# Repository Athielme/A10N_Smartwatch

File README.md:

# A10N_Smartwatch
Created for the Purdue MILESTONES Smartwatch course, Summer 2020

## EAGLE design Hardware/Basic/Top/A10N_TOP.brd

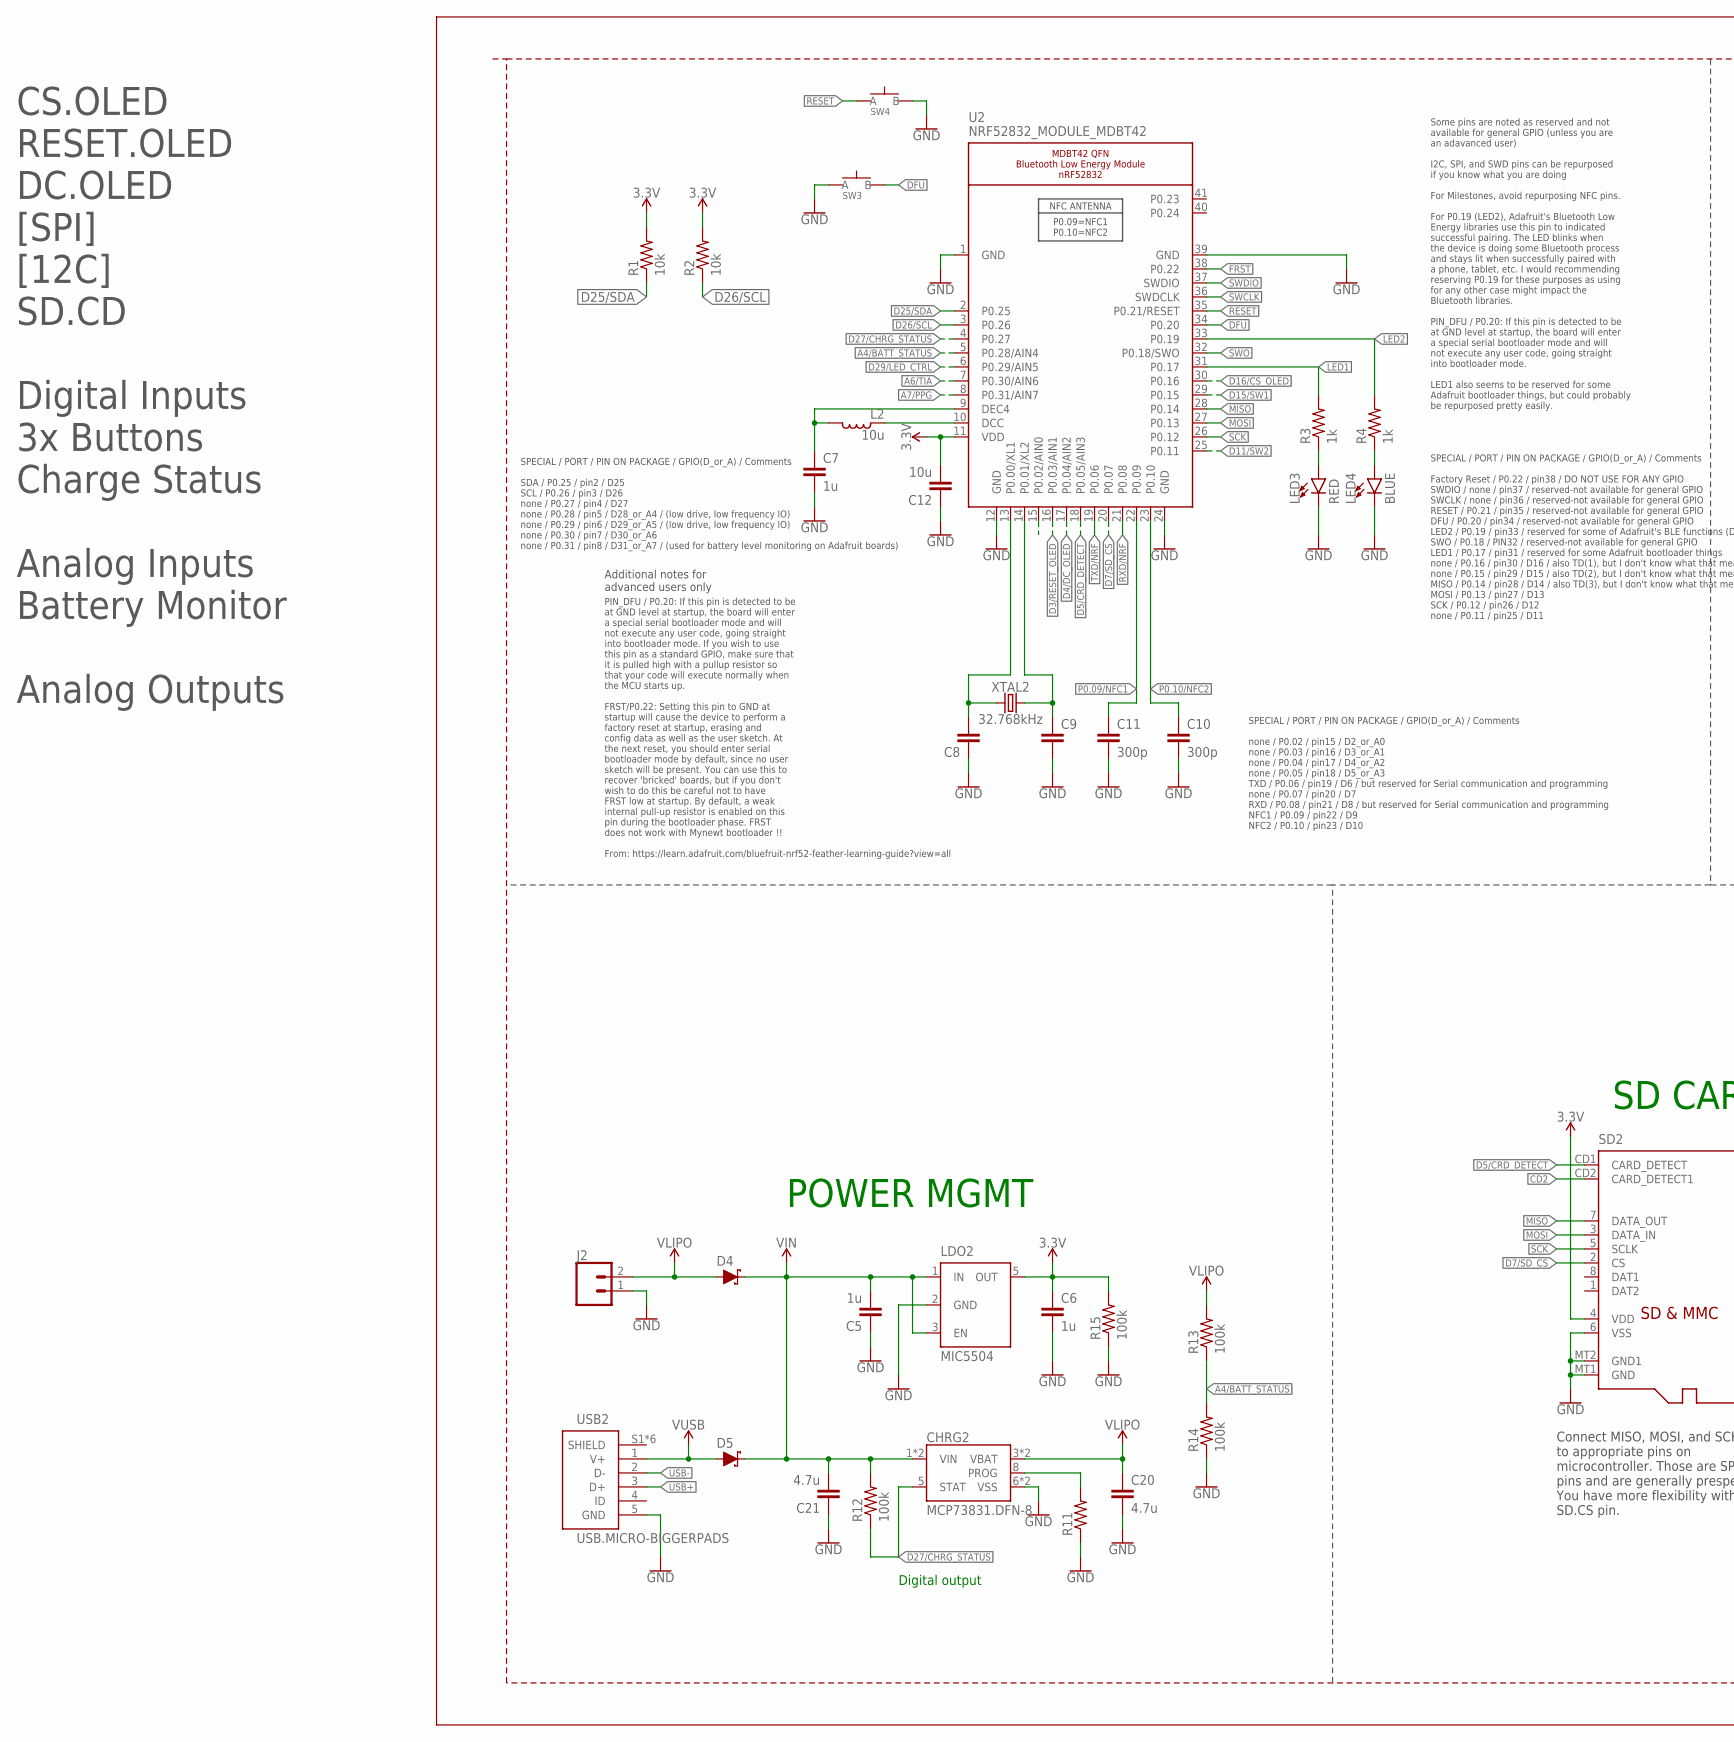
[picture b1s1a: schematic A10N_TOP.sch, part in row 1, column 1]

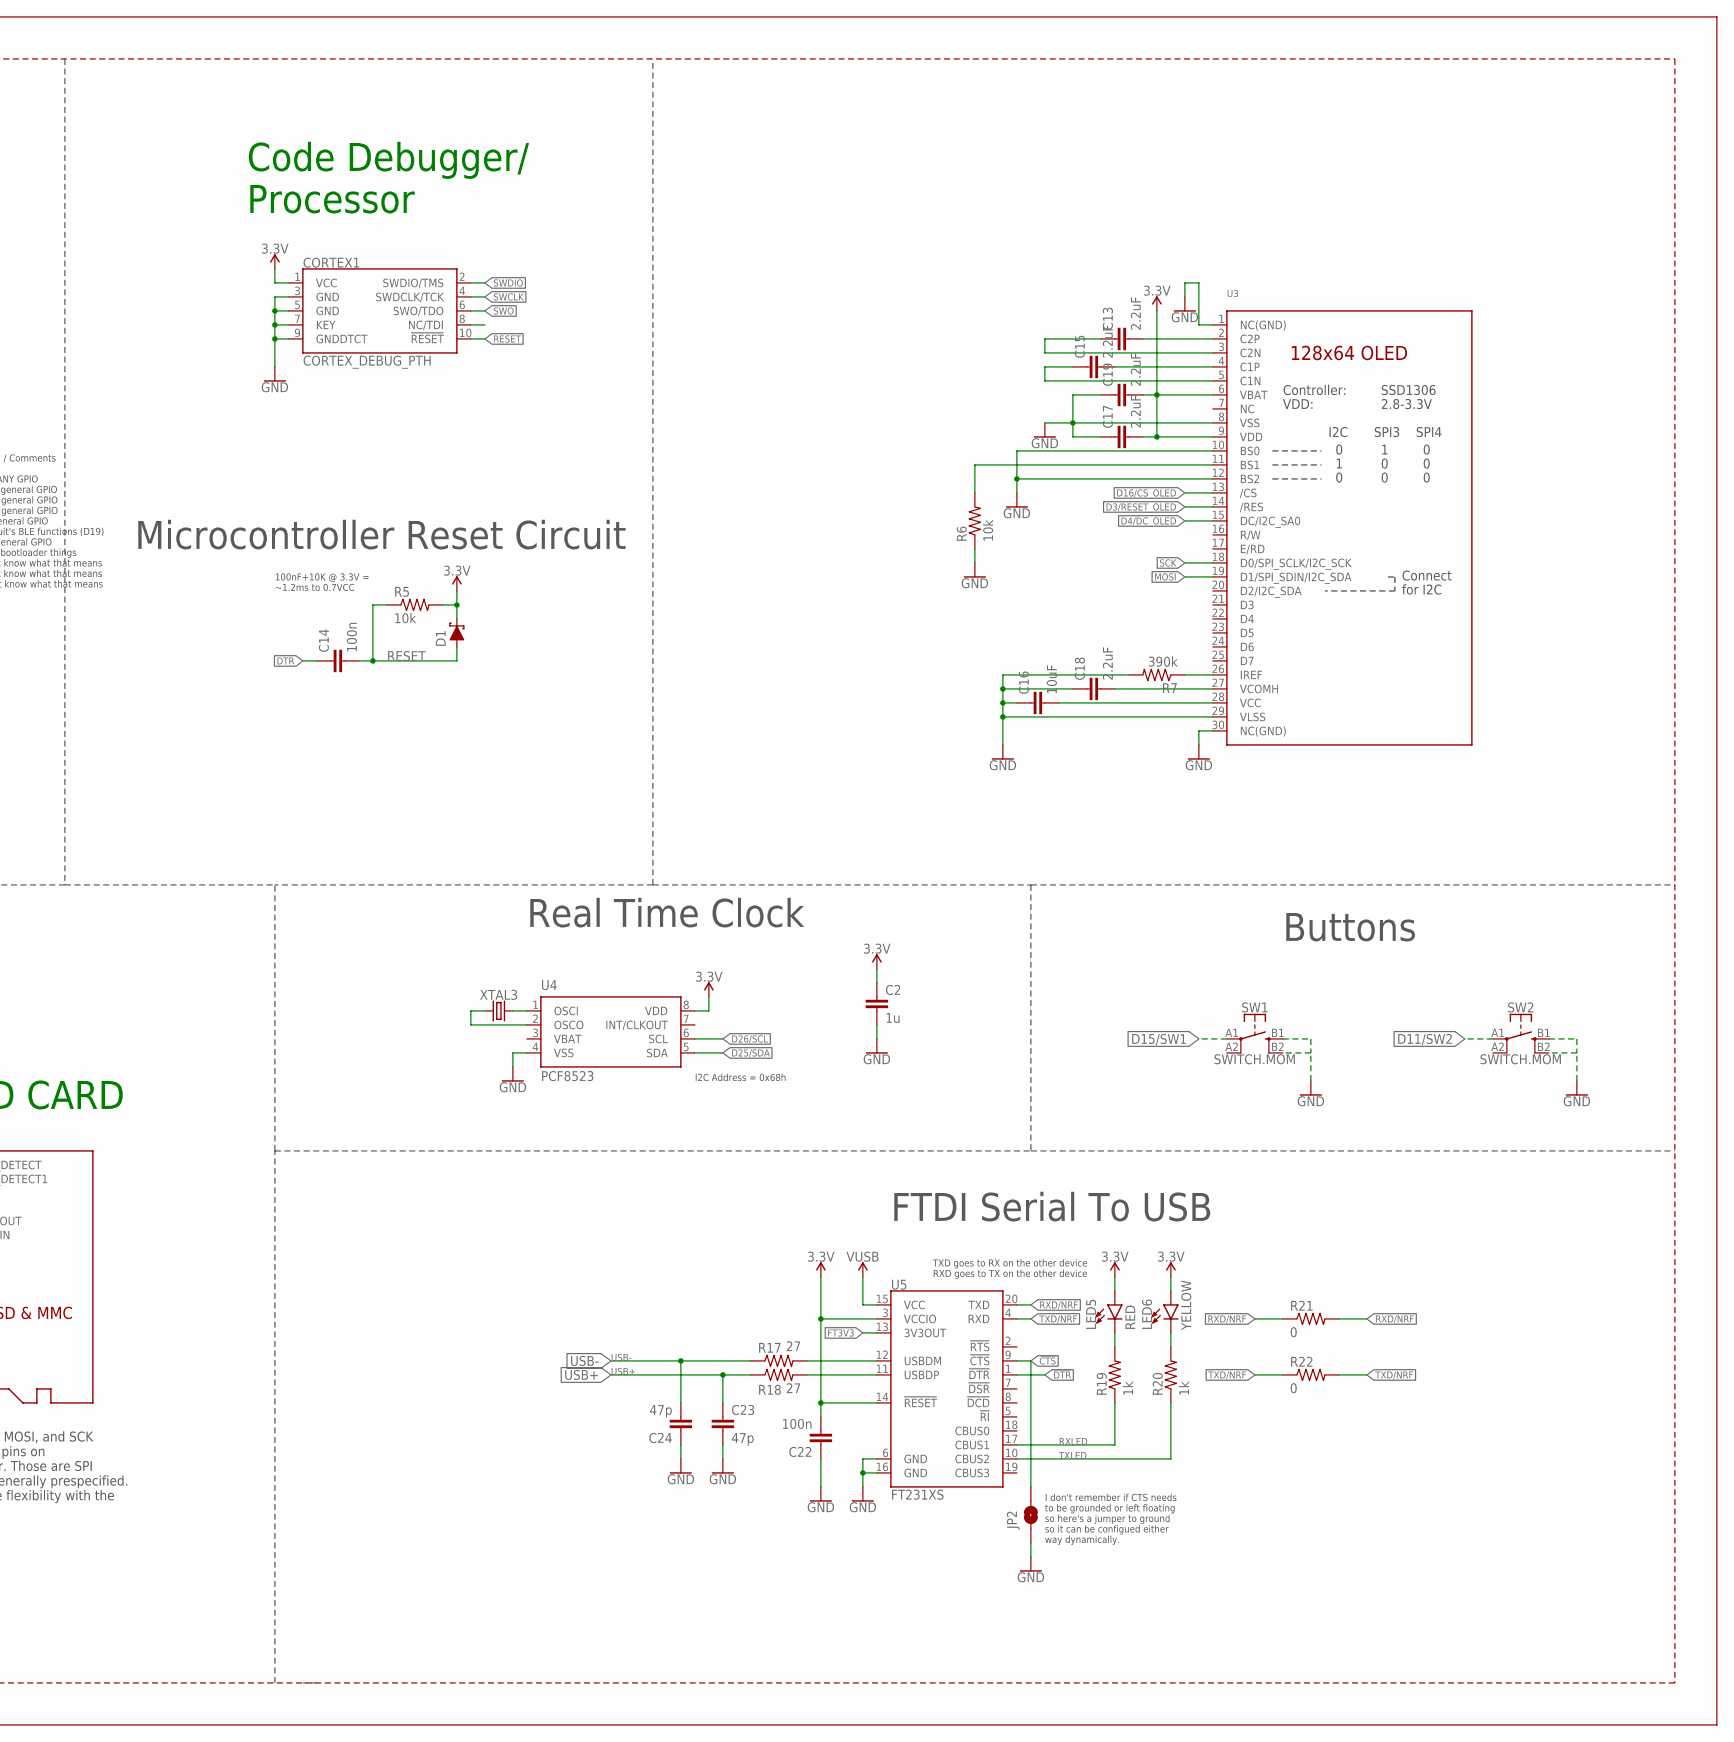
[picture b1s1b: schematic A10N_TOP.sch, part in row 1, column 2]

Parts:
C2, C5, C6, C7: 1u; C0603
C8, C9: CAPACITOR0603; C0603
C10, C11: 300p; C0603
C12: 10u; C0805
C13, C15, C17, C18, C19: 2.2uF; C0402
C14, C22: 100n; C0603
C16: 10uF; C0603
C20, C21: 4.7u; C0603
C23, C24: 47p; C0603
CHRG2: MCP73831.DFN-8; DFN-8-2X3MM
CORTEX1: CORTEX_DEBUG_PTH; 2X5-PTH-1.27MM
D1, D4, D5: SCHOTTKY-USC; USC
J2: CONN_02; 1X02
JP2: JUMPER-SMT_2_NO_SILK; SMT-JUMPER_2_NO_SILK
L2: 10u; L0603
LDO2: MIC5504; SOT23-5@1
LED3, LED5: RED; LED-0603
LED4: BLUE; LED-0603
LED6: YELLOW; LED-0603
R1, R2, R5, R6: 10k; R0603
R3, R4, R19, R20: 1k; R0603
R7: 390k; R0603
R11: RESISTOR0603; R0603
R12, R13, R14, R15: 100k; R0603
R17, R18: 27; R0603
R21, R22: 0; R0603
SD2: MICROSD
SW1, SW2: SWITCH.MOM; TACTILE_SWITCH_SMD_6.2MM_TALL
SW3, SW4: SPST-PTS830GG140-COPY.1-3; BUTTON-GULLWING
U2: NRF52832_MODULE_MDBT42; BLE_MODULE_RAYTAC_MDBT42
U3: DISP_OLED_UG-2864HSWEG01-NO-WRAPAROUND; UG-2864HSWEG01_0.96IN_NO-WRAPAROUND
U4: PCF8523; SO8; DIGIKEY 568-5306-1-ND
U5: FT231XS; SSOP20_L
USB2: USB.MICRO-BIGGERPADS; USB-MICRO-01.BIGGERPADS
XTAL2: 32.768kHz; 2-SMD.NOLEAD.2.0MMTO1.2MM
XTAL3: 32.7680kHz; 2-SMD.NOLEAD.2.0MMTO1.2MM

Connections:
3.3V: C2.1, C6.1, C12.2, C17.2, C19.2, C22.2, CORTEX1.1 (VCC), D1.- (C), LDO2.5 (OUT), LED5.A, LED6.A, R1.2, R2.2, R5.2, R15.2, SD2.4 (VDD), U2.11 (VDD), U3.6 (VBAT), U3.9 (VDD), U4.8 (VDD), U5.3 (VCCIO), U5.14 (!RESET)
!CTS: JP2.2, U5.9 (!CTS)
!DTR: U5.1 (!DTR)
A4/BATT_STATUS: R13.1, R14.2, U2.5 (P0.28/AIN4)
A6/TIA: U2.7 (P0.30/AIN6)
A7/PPG: U2.8 (P0.31/AIN7)
CD2: SD2.CD2 (CARD_DETECT1)
D3/RESET_OLED: U2.16 (P0.03/AIN1), U3.14 (/RES)
D4/DC_OLED: U2.17 (P0.04/AIN2), U3.15 (DC/I2C_SA0)
D5/CRD_DETECT: SD2.CD1 (CARD_DETECT), U2.18 (P0.05/AIN3)
D7/SD_CS: SD2.2 (CS), U2.20 (P0.07)
D11/SW2: SW2.A1 (1), U2.25 (P0.11)
D15/SW1: SW1.A1 (1), U2.29 (P0.15)
D16/CS_OLED: U2.30 (P0.16), U3.13 (/CS)
D25/SDA: R1.1, U2.2 (P0.25), U4.5 (SDA)
D26/SCL: R2.1, U2.3 (P0.26), U4.6 (SCL)
D27/CHRG_STATUS: CHRG2.5 (STAT), R12.1, U2.4 (P0.27)
D29/LED_CTRL: U2.6 (P0.29/AIN5)
DFU: SW3.3 (B), U2.34 (P0.20)
DTR: C14.1
FRST: U2.38 (P0.22)
FT3V3: U5.13 (3V3OUT)
GND: C2.2, C5.1, C6.2, C7.2, C8.1, C9.2, C10.2, C11.2, C12.1, C16.1, C17.1, C18.1, C19.1, C20.2, C21.1, C22.1, C23.2, C24.1, CHRG2.6 (VSS), CHRG2.EP (VSS), CORTEX1.3 (GND), CORTEX1.5 (GND), CORTEX1.7 (KEY), CORTEX1.9 (GNDDTCT), J2.1, JP2.1, LDO2.2 (GND), LED3.C, LED4.C, R6.1, R7.2, R11.1, R14.1, R15.1, SD2.6 (VSS), SD2.MT1 (GND), SD2.MT2 (GND1), SW1.B1 (3), SW1.B2 (4), SW2.B1 (3), SW2.B2 (4), SW3.1 (A), SW4.3 (B), U2.1 (GND), U2.12 (GND), U2.24 (GND), U2.39 (GND), U3.1 (NC(GND)), U3.8 (VSS), U3.10 (BS0), U3.12 (BS2), U3.29 (VLSS), U3.30 (NC(GND)), U4.4 (VSS), U5.6 (GND), U5.16 (GND), USB2.5 (GND)
LED1: R3.2, U2.31 (P0.17)
LED2: R4.2, U2.33 (P0.19)
MISO: SD2.7 (DATA_OUT), U2.28 (P0.14)
MOSI: SD2.3 (DATA_IN), U2.27 (P0.13), U3.19 (D1/SPI_SDIN/I2C_SDA)
unnamed: R6.2, U3.11 (BS1)
unnamed: R7.1, U3.26 (IREF)
unnamed: C13.2, U3.2 (C2P)
unnamed: C8.2, U2.13 (P0.00/XL1), XTAL2.P$1 (1)
unnamed: C13.1, U3.3 (C2N)
unnamed: C9.1, U2.14 (P0.01/XL2), XTAL2.P$2 (2)
unnamed: C15.2, U3.4 (C1P)
unnamed: C15.1, U3.5 (C1N)
unnamed: LED3.A, R3.1
unnamed: LED4.A, R4.1
unnamed: L2.1, U2.10 (DCC)
unnamed: C7.1, L2.2, U2.9 (DEC4)
unnamed: C16.2, U3.28 (VCC)
unnamed: C18.2, U3.27 (VCOMH)
unnamed: CHRG2.8 (PROG), R11.2
unnamed: R17.2, U5.12 (USBDM)
unnamed: R18.2, U5.11 (USBDP)
unnamed: LED5.C, R19.2
unnamed: LED6.C, R20.2
unnamed: U4.2 (OSCO), XTAL3.P$1 (1)
unnamed: U4.1 (OSCI), XTAL3.P$2 (2)
P0.09/NFC1: C11.1, U2.22 (P0.09)
P0.10/NFC2: C10.1, U2.23 (P0.10)
RESET: C14.2, CORTEX1.10 (!RESET), D1.+ (A), R5.1, SW4.1 (A), U2.35 (P0.21/RESET)
RXD/NRF: U2.21 (P0.08), U5.20 (TXD)
RXLED: R19.1, U5.17 (CBUS1)
SCK: SD2.5 (SCLK), U2.26 (P0.12), U3.18 (D0/SPI_SCLK/I2C_SCK)
SWCLK: CORTEX1.4 (SWDCLK/TCK), U2.36 (SWDCLK)
SWDIO: CORTEX1.2 (SWDIO/TMS), U2.37 (SWDIO)
SWO: CORTEX1.6 (SWO/TDO), U2.32 (P0.18/SWO)
TXD/NRF: U2.19 (P0.06), U5.4 (RXD)
TXLED: R20.1, U5.10 (CBUS2)
USB+: C23.1, R18.1, USB2.3 (D+)
USB-: C24.2, R17.1, USB2.2 (D-)
VBAT: U4.3 (VBAT)
VIN: C5.2, C21.2, CHRG2.1 (VIN), CHRG2.2 (VIN), D4.- (C), D5.- (C), LDO2.1 (IN), LDO2.3 (EN), R12.2
VLIPO: C20.1, CHRG2.3 (VBAT), CHRG2.4 (VBAT), D4.+ (A), J2.2, R13.2
V_USB: D5.+ (A), U5.15 (VCC), USB2.1 (V+)

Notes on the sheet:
Microcontroller Reset Circuit
100nF+10K @ 3.3V = ~1.2ms to 0.7VCC
SPECIAL / PORT / PIN ON PACKAGE / GPIO(D_or_A) / Comments SDA / P0.25 / pin2 / D25 SCL / P0.26 / pin3 / D26 none / P0.27 / pin4 / D27 none / P0.28 / pin5 / D28_or_A4 / (low drive, low frequency IO) none / P0.29 / pin6 / D29_or_A5 / (low drive, low frequency IO) none / P0.30 / pin7 / D30_or_A6 none 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
SPECIAL / PORT / PIN ON PACKAGE / GPIO(D_or_A) / Comments none / P0.02 / pin15 / D2_or_A0 none / P0.03 / pin16 / D3_or_A1 none / P0.04 / pin17 / D4_or_A2 none / P0.05 / pin18 / D5_or_A3 TXD / P0.06 / pin19 / D6 / but reserved for Serial communication and programming none / P0.07 / pin20 / D7 RXD / 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
SPECIAL / PORT / PIN ON PACKAGE / GPIO(D_or_A) / Comments Factory Reset / P0.22 / pin38 / DO NOT USE FOR ANY GPIO SWDIO / none / pin37 / reserved-not available for general GPIO SWCLK / none / pin36 / reserved-not available for general GPIO RESET / P0.21 / pin35 / reserved-not available for general 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
Some pins are noted as reserved and not available for general GPIO (unless you are an adavanced user) I2C, SPI, and SWD pins can be repurposed if you know what you are doing For Milestones, avoid repurposing NFC pins. For P0.19 (LED2), Adafruit's Bluetooth Low Energy libraries use this pin to indic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
PIN_DFU / P0.20: If this pin is detected to be at GND level at startup, the board will enter a special serial bootloader mode and will not execute any user code, going straight into bootloader mode. If you wish to use this pin as a standard GPIO, make sure that it is pulled high with a pullup resis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
Additional notes for advanced users only
Connect MISO, MOSI, and SCK to appropriate pins on microcontroller. Those are SPI pins and are generally prespecified. You have more flexibility with the SD.CS pin.
Code Debugger/ Processor
SD CARD
POWER MGMT
CS.OLED RESET.OLED DC.OLED [SPI] [12C] SD.CD Digital Inputs 3x Buttons Charge Status Analog Inputs Battery Monitor Analog Outputs
TXD goes to RX on the other device RXD goes to TX on the other device
I don't remember if CTS needs to be grounded or left floating so here's a jumper to ground so it can be configued either way dynamically.
Buttons
FTDI Serial To USB
Digital output
I2C Address = 0x68h
Real Time Clock

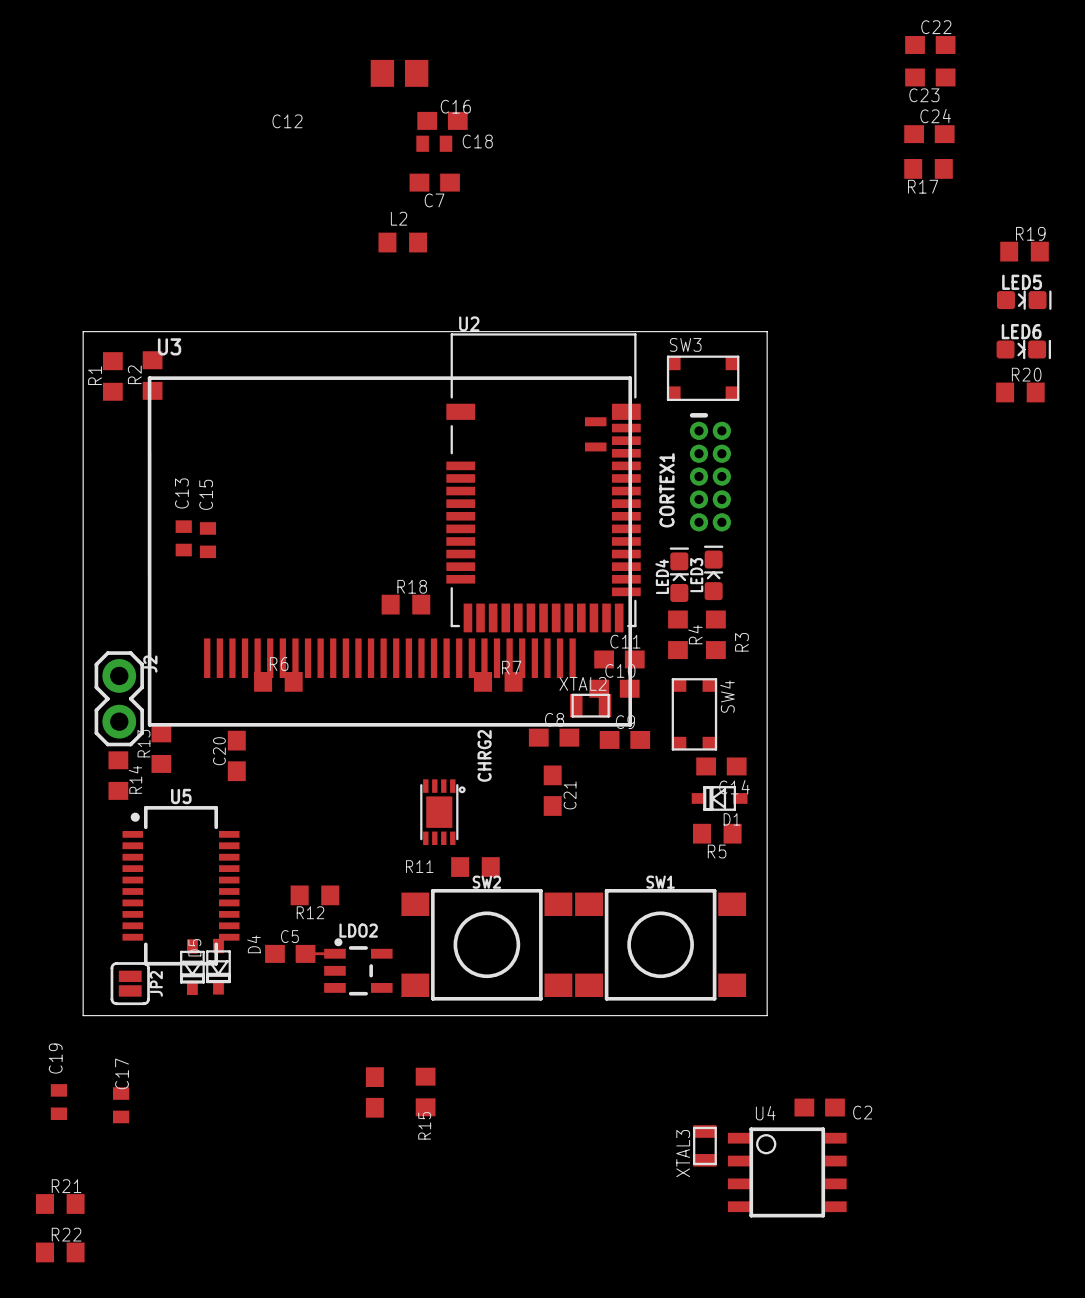
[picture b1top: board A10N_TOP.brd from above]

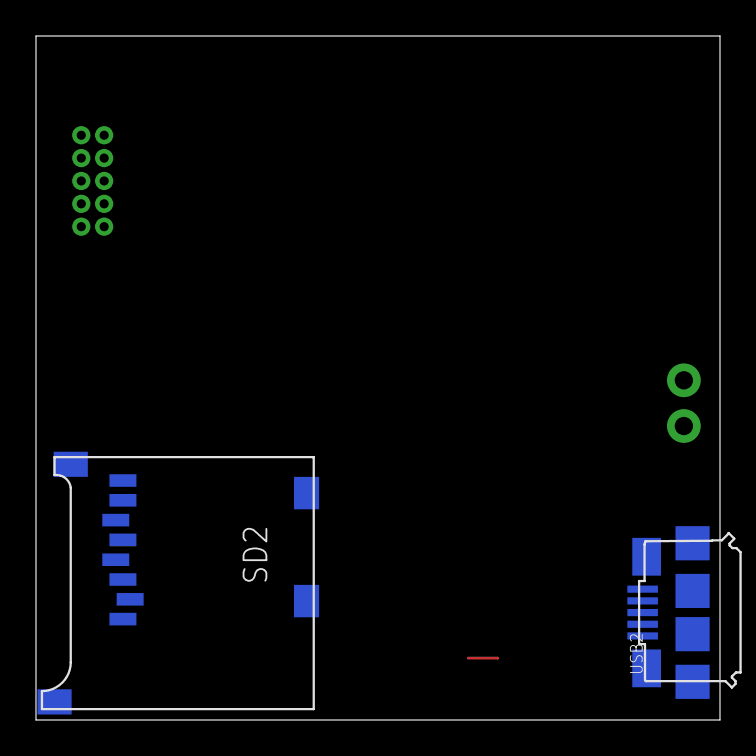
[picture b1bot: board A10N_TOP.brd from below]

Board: 2 copper layers, 38.0 x 38.0 mm, 64 parts (2 on the bottom side), 56 nets.

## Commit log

2020-06-30 Added featues list word document
2020-06-30 Changed repo name and added features to Device_Features.docx
2020-07-01 created TOP, BOTTOM, and PPG-MODULE BOM files and folders
2020-07-07 Updated .gitignore to include DS files
2020-07-14 Added Top Board
2020-07-14 Added bottom board
2020-07-14 Connected SD Card, LEDs,
2020-07-29 Added PPG and Bottom Boards
